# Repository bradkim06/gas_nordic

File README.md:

# Industrial Gas Monitor Firmware (nRF52832 + Zephyr)

Firmware version **1.0.2** for HHS's portable industrial gas monitor. The
application runs on a custom nRF52832 board, measures multiple gases, and
transmits real-time readings over Bluetooth® Low Energy. Environmental data is
fused with the Bosch BSEC2 library to provide indoor air-quality indicators in
addition to electrochemical gas concentrations.

---

## Table of contents

1. [Key features](#key-features)
2. [Hardware overview](#hardware-overview)
3. [Supported measurements](#supported-measurements)
4. [Firmware architecture](#firmware-architecture)
5. [Build and flash](#build-and-flash)
6. [Bluetooth protocol](#bluetooth-protocol)
7. [Calibration & persistent settings](#calibration--persistent-settings)
8. [Reference tables](#reference-tables)
9. [License](#license)

---

## Key features

- **Multi-gas sensing** – Electrochemical front-end for oxygen and a selectable
  toxic gas channel (NO₂, CO, H₂S, Cl₂, NH₃, etc.) with temperature
  compensation and dynamic calibration algorithms.【F:src/gas.c†L1-L212】
- **Environmental monitoring** – Integrated BME68x support with Bosch BSEC2
  fusion to derive temperature, humidity, pressure, IAQ, equivalent CO₂, and
  VOC indices. BSEC state is saved to flash for consistent long-term behavior.
  【F:drivers/bme68x_iaq/bme68x_iaq.c†L40-L460】【F:src/settings.c†L1-L137】
- **Bluetooth LE connectivity** – Custom 128-bit GATT service publishes
  semicolon-delimited measurements every 10 seconds and accepts configuration
  commands from a companion application.【F:src/bluetooth.h†L5-L45】【F:src/bluetooth.c†L520-L585】
- **Robust low-power platform** – Built on Zephyr RTOS (nRF Connect SDK v2.4.2)
  with watchdog, power management, persistent storage, and board-specific
  optimizations.【F:prj.conf†L1-L110】

## Hardware overview

- **Target SoC:** Nordic Semiconductor nRF52832 (ARM® Cortex®-M4F, BLE 5).
- **Custom board definition:** `boards/arm/hhs_nrf52832` (schematic and layout
  included in `doc/`).【F:boards/arm/hhs_nrf52832/hhs_nrf52832.yaml†L1-L53】
- **Latest hardware pack:** `doc/gas_nrf52832_rev1.0.1.pdf` with matching
  schematic `doc/gas_nrf52832_sch_rev0.1.0.pdf`.
- **Peripheral highlights:**
  - Bosch BME688/BME680 environmental sensor on I²C.
  - Dual-channel electrochemical sensor front-end via SAADC.
  - Battery gauge through voltage divider + ADC.
  - RGB status LED and watchdog support.

## Supported measurements

| Domain                | Reported values                                              |
| --------------------- | ------------------------------------------------------------ |
| Electrochemical gas   | Oxygen concentration (%VOL) and one selectable toxic gas in
|                       | ppm, both temperature compensated and filtered.【F:src/gas.c†L1-L212】 |
| Environmental         | Temperature (°C), relative humidity (%RH), barometric
|                       | pressure (Pa), IAQ score, equivalent CO₂ (ppm), and breath
|                       | VOC index via BSEC2.【F:drivers/bme68x_iaq/bme68x_iaq.c†L40-L460】 |
| Power                 | Battery percentage derived from loaded voltage profile.
| BLE telemetry         | Timestamped payload streamed every 10 seconds (default).

## Firmware architecture

The firmware is organized into cooperative Zephyr threads and kernel events. A
high-level flow is shown below:

```mermaid
---
title: Portable Gas Monitor Firmware Flow
---
stateDiagram-v2
    direction TB
    [*] --> ZephyrRTOS
    ZephyrRTOS --> BME68x_BSEC
    ZephyrRTOS --> Electrochemical_ADC
    ZephyrRTOS --> BluetoothLE

    state ZephyrRTOS {
        state BME68x_BSEC {
            direction LR
            initBSEC --> readEnvironmental : 3 s
            initBSEC --> computeIAQ : 60 s
        }
        state Electrochemical_ADC {
            direction TB
            sampleADC --> tempCompensation
            tempCompensation --> gasConversion
            gasConversion --> dynamicCalibration
        }
        state BluetoothLE {
            direction LR
            initialize --> advertise
            advertise --> connected
            connected --> notifyData : 10 s
        }
    }
```

Key modules reside in `src/` (application logic), `drivers/bme68x_iaq/`
(BSEC2 integration), and `lib/` (Bosch libraries). Threads communicate via
Zephyr events for deterministic BLE publishing and alarm handling.

## Build and flash

1. **Install prerequisites**
   - [nRF Connect SDK v2.4.2](https://developer.nordicsemi.com/nRF_Connect_SDK/doc/2.4.2/nrf/index.html)
     with the Zephyr toolchain, `west`, and SEGGER J-Link tools.
   - Bosch BSEC2 library files are already provided under `lib/`.
2. **Fetch the source**
   ```bash
   git clone https://github.com/<your-org>/gas_nordic.git
   cd gas_nordic
   west init -l .
   west update
   ```
3. **Build**
   ```bash
   west build -b hhs_nrf52832 .
   ```
   The output image is generated at `build/zephyr/zephyr.hex`.
4. **Flash**
   ```bash
   west flash
   ```
   or, to use Nordic's command-line tools directly:
   ```bash
   ./flash.sh
   ```
   (`flash.sh` performs a chip erase and programs the generated HEX via
   `nrfjprog`).【F:flash.sh†L1-L5】

## Bluetooth protocol

The device exposes a proprietary 128-bit primary service (`0000FFF0-0000-1000-8000-00805F9B34FB`).【F:src/bluetooth.h†L9-L26】

| Characteristic | UUID                                      | Properties | Description |
| -------------- | ----------------------------------------- | ---------- | ----------- |
| Measurement    | `0000FFF1-0000-1000-8000-00805F9B34FB`    | Notify     | Periodic payload `O2;Gas;Battery;Temp;Pressure;Humidity` separated by semicolons, integers scaled as `<val1>.<val2>` where applicable.【F:src/bluetooth.c†L536-L576】 |
| Command        | `0000FFF2-0000-1000-8000-00805F9B34FB`    | Write      | ASCII commands for calibration and configuration: `O2=<percent>`, `NO2=<ppm>`, `BT=<name>`.【F:src/bluetooth.c†L60-L124】 |

Notifications are issued when a connection is active and the client enables
CCCD. Each update corresponds to the latest sensor snapshot and is throttled to
the configured 10 s publishing interval.

## Calibration & persistent settings

- **Dynamic calibration** continuously refines oxygen and toxic gas baselines by
  monitoring derivative stability, expected ranges, and board temperature.
  Manual calibration can be triggered by writing to the command characteristic as
  described above.【F:src/gas.c†L1-L212】【F:src/bluetooth.c†L60-L124】
- **Persistent storage** uses Zephyr's settings/NVS subsystem to retain BSEC
  state, sensor calibration voltages, and the advertised Bluetooth name across
  reboots.【F:src/settings.c†L1-L200】
- **Battery reporting** samples SAADC channels and converts them into a
  percentage using empirically tuned thresholds (see `src/battery.c`).

## Reference tables

### Oxygen concentration guide

| Category                    | Concentration range | Notes |
| --------------------------- | ------------------- | ----- |
| High oxygen                 | &gt; 24 %             | Elevated combustion risk. |
| Normal air                  | 20.9 %              | Nominal breathable atmosphere. |
| Elevated exposure risk      | 19.5 – 20.9 %       | Monitor for dilution hazards. |
| Low oxygen                  | 16 – 19.5 %         | Impaired cognition and physical performance. |
| Anoxic                      | &lt; 16 %             | Life-threatening within minutes. |

### Indoor air quality (IAQ) interpretation

| IAQ index | Air quality           | Suggested action |
| --------- | --------------------- | ---------------- |
| 0 – 50    | Excellent             | None required. |
| 51 – 100  | Good                  | None required. |
| 101 – 150 | Lightly polluted      | Ventilate if convenient. |
| 151 – 200 | Moderately polluted   | Increase ventilation with clean air. |
| 201 – 250 | Heavily polluted      | Identify contamination source, improve airflow. |
| 251 – 350 | Severely polluted     | Restrict access, maximize ventilation. |
| &gt; 351    | Extremely polluted    | Avoid occupancy until levels normalize. |

### CO₂ comfort levels

| Level | Description                        | ppm |
| :---: | ---------------------------------- | --- |
| 😆    | Healthy outdoor reference          | 350 |
| 😀    | Healthy indoor climate             | 600 |
| 🙂    | Acceptable indoors                 | 800 |
| 🙁    | Ventilation desirable              | 1000 |
| 😩    | Ventilation necessary              | 1200 |
| 😡    | Noticeable health effects          | 2000 |
| ⚠️    | Dangerous for prolonged exposure | 5000 |

### VOC hygiene guidance

| Rating    | Recommendation                                 | Exposure duration | TVOC (ppm) |
| --------- | ---------------------------------------------- | ----------------- | ---------- |
| Excellent | Target value                                    | Unlimited         | 0 – 0.065 |
| Good      | Ventilation recommended                         | Unlimited         | 0.065 – 0.22 |
| Moderate  | Increase ventilation, inspect for sources       | &lt; 12 months       | 0.22 – 0.66 |
| Poor      | Intensify ventilation, locate emission sources  | &lt; 1 month         | 0.66 – 2.2 |
| Unhealthy | Immediate ventilation required                  | Hours             | 2.2 – 5.5 |

## License

Distributed under the terms of the [MIT License](LICENSE). Bosch BSEC2 library
usage is subject to its proprietary license (see `lib/Bosch-BSEC2-Library`).

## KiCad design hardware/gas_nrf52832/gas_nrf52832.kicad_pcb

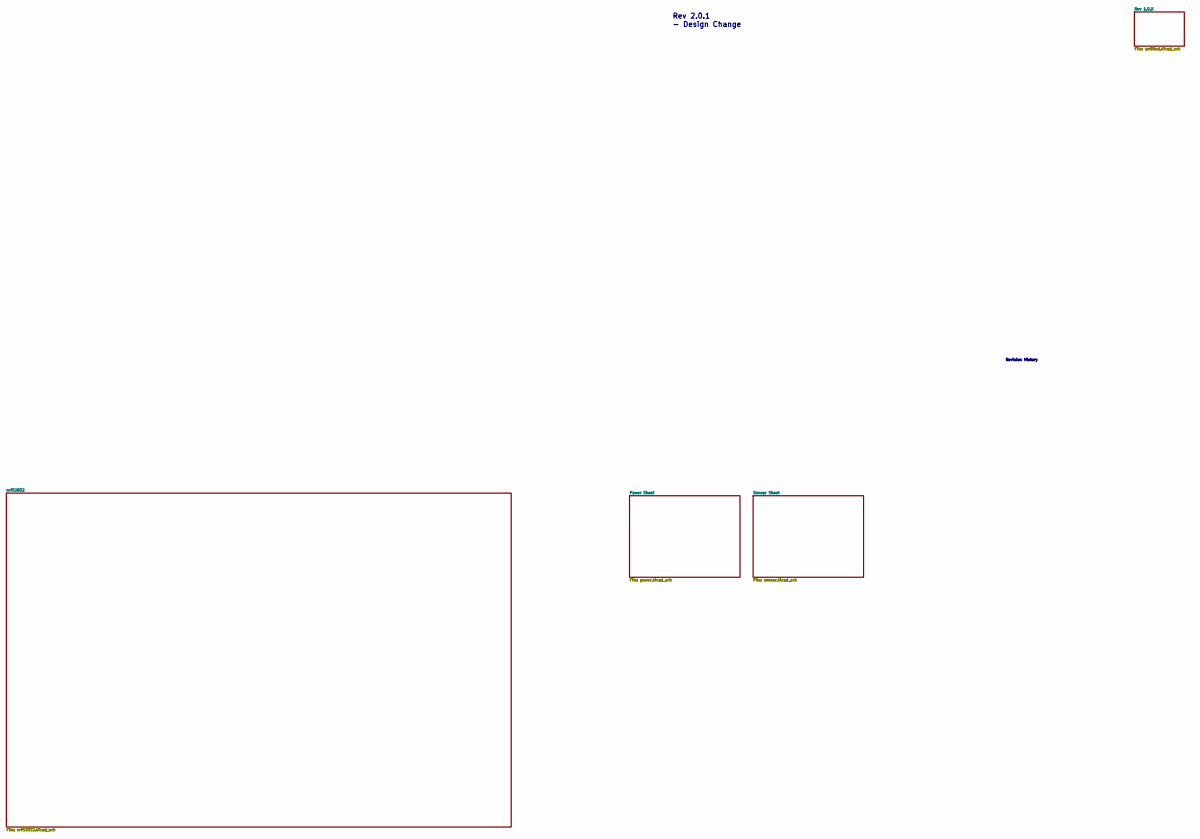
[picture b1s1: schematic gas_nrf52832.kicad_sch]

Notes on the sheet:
Revision History
Rev 2.0.1 - Design Change

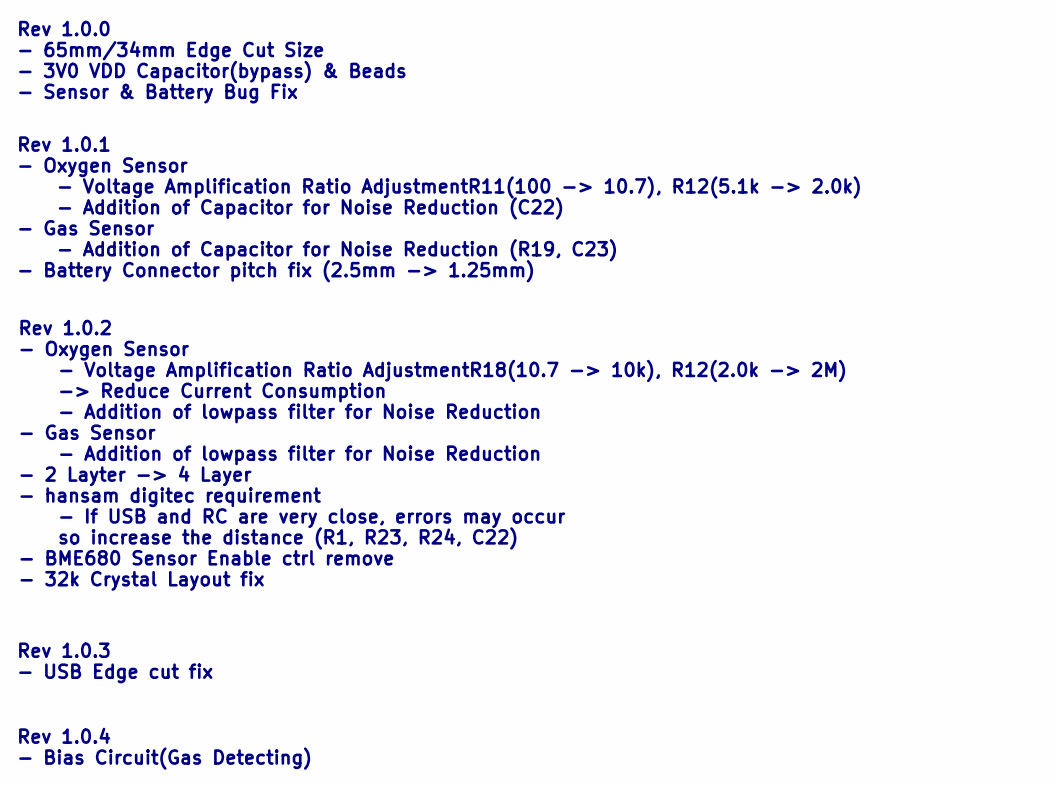
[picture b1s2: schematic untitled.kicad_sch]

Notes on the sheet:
Rev 1.0.2 - Oxygen Sensor - Voltage Amplification Ratio AdjustmentR18(10.7 -> 10k), R12(2.0k -> 2M) -> Reduce Current Consumption - Addition of lowpass filter for Noise Reduction - Gas Sensor - Addition of lowpass filter for Noise Reduction - 2 Layter -> 4 Layer - hansam digitec requirement - If US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
Rev 1.0.3 - USB Edge cut fix
Rev 1.0.0 - 65mm/34mm Edge Cut Size - 3V0 VDD Capacitor(bypass) & Beads - Sensor & Battery Bug Fix
Rev 1.0.1 - Oxygen Sensor - Voltage Amplification Ratio AdjustmentR11(100 -> 10.7), R12(5.1k -> 2.0k) - Addition of Capacitor for Noise Reduction (C22) - Gas Sensor - Addition of Capacitor for Noise Reduction (R19, C23) - Battery Connector pitch fix (2.5mm -> 1.25mm)
Rev 1.0.4 - Bias Circuit(Gas Detecting)

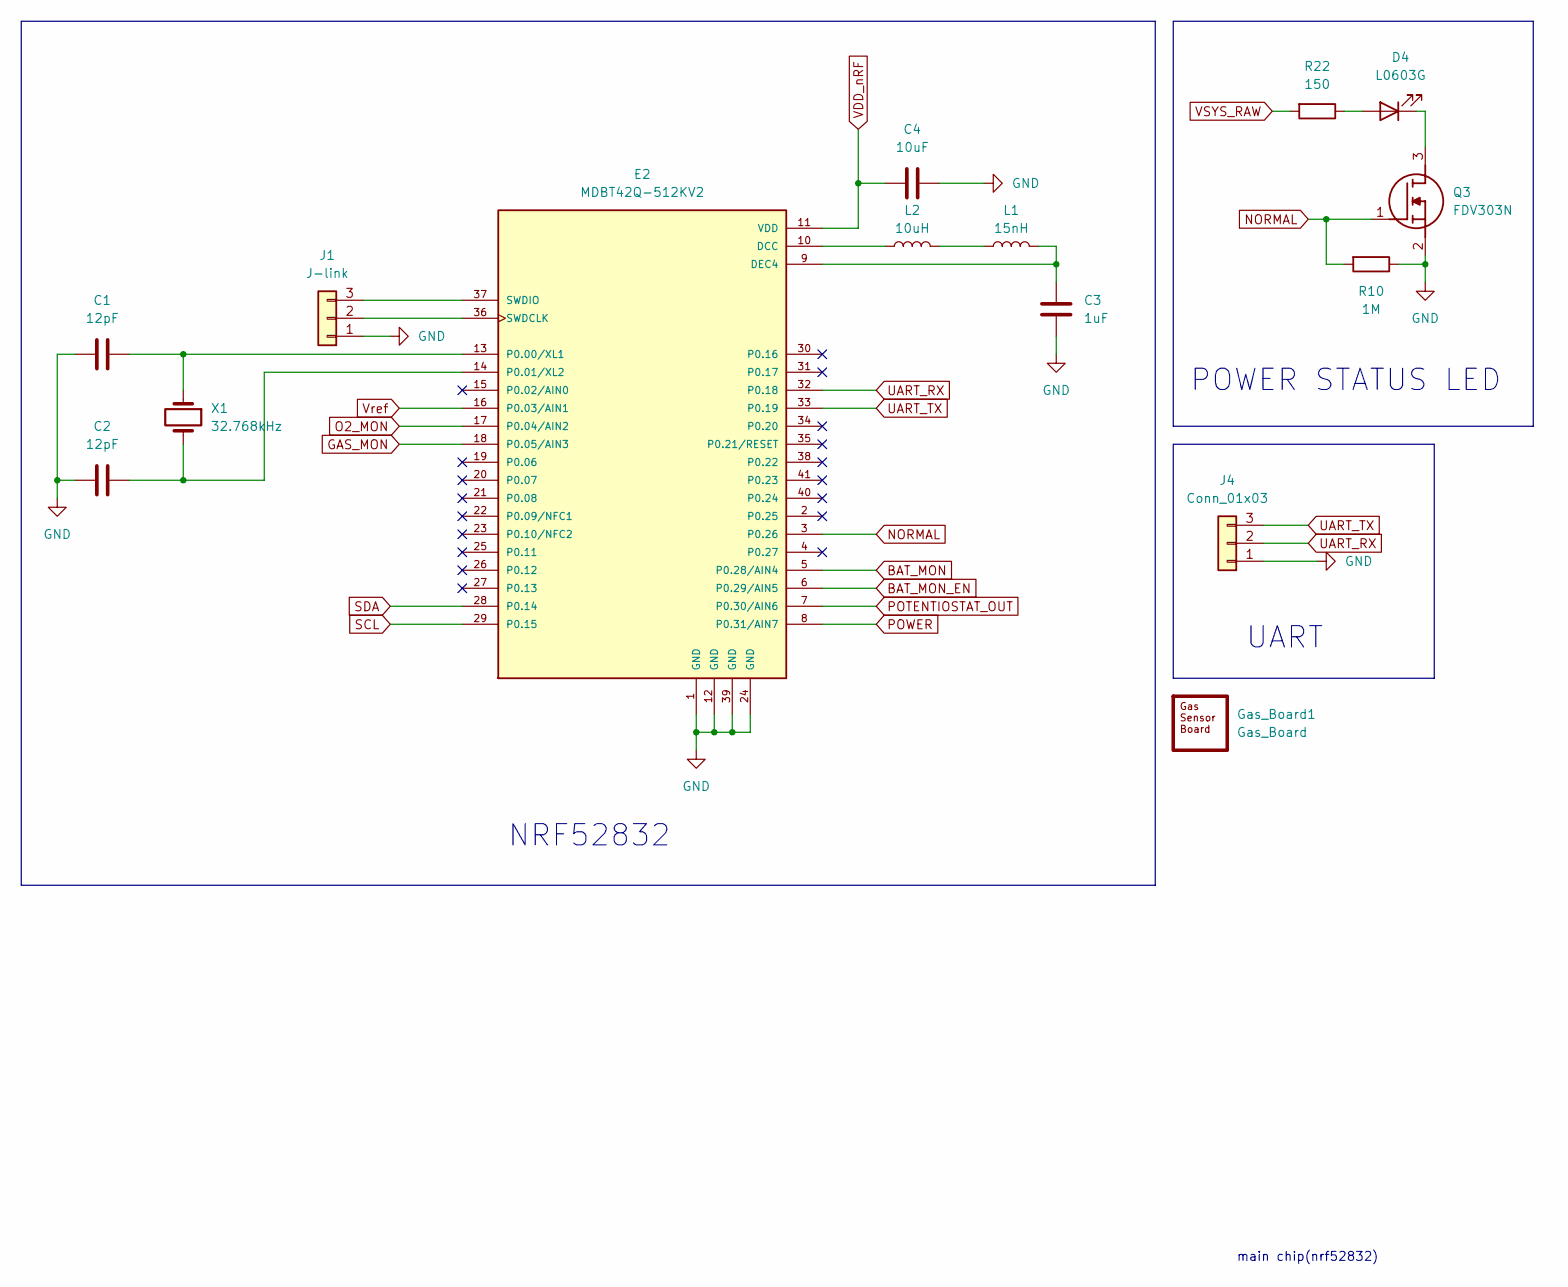
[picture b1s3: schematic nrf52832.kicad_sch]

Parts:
C1, C2: 12pF; C_0402_1005Metric; Manufacturer_Part_Number CL05C120JB5NNNC
C3: 1uF; C_0402_1005Metric; Manufacturer_Part_Number GRM155C71A105ME11D
C4: 10uF; C_0402_1005Metric; Manufacturer_Part_Number GRM155C80J106ME11D
D4: L0603G; WP1533BQ; Manufacturer_Part_Number WP1533BQ/GD
E2: MDBT42Q-512KV2; RAYTAC_MDBT42Q-512KV2; PARTREV J
Gas_Board1: Gas_Board; gas_nordic_edge
J1: J-link; PinHeader_1x03_P2.54mm_Vertical
J4: Conn_01x03; PinHeader_1x03_P2.54mm_Vertical
L1: 15nH; L_0402_1005Metric; Manufacturer_Part_Number MLG1005S15NJT000
L2: 10uH; L_0603_1608Metric; Manufacturer_Part_Number LQM18FN100M00D
Q3: FDV303N; SOT96P237X111-3N; Manufacturer_Part_Number FDV303N; Mouser Part Number 512-FDV303N
R10: 1M; R_0402_1005Metric; Manufacturer_Part_Number RC0402FR-071ML
R22: 150; R_0402_1005Metric; Manufacturer_Part_Number RM04FTN1500
X1: 32.768kHz; Crystal_SMD_3215-2Pin_3.2x1.5mm; Manufacturer_Part_Number FC-135 32.7680KA-A5

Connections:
BAT_MON: E2.5 (P0.28/AIN4); also elsewhere on the board
BAT_MON_EN: E2.6 (P0.29/AIN5); also elsewhere on the board
GAS_MON: E2.18 (P0.05/AIN3); also elsewhere on the board
GND: C1.1, C2.1, C3.2, C4.2, E2.1 (GND), E2.12 (GND), E2.24 (GND), E2.39 (GND), J1.1, J4.1, Q3.2 (S), R10.1; also elsewhere on the board
NORMAL: E2.3 (P0.26), Q3.1 (G), R10.2
unnamed: D4.2 (A), R22.1
unnamed: D4.1 (K), Q3.3 (D)
unnamed: E2.10 (DCC), L2.1
unnamed: C3.1, E2.9 (DEC4), L1.2
unnamed: C1.2, E2.13 (P0.00/XL1), X1.1
unnamed: C2.2, E2.14 (P0.01/XL2), X1.2
unnamed: E2.36 (SWDCLK), J1.2
unnamed: E2.37 (SWDIO), J1.3
unnamed: L1.1, L2.2
O2_MON: E2.17 (P0.04/AIN2); also elsewhere on the board
POTENTIOSTAT_OUT: E2.7 (P0.30/AIN6); also elsewhere on the board
POWER: E2.8 (P0.31/AIN7); also elsewhere on the board
SCL: E2.29 (P0.15); also elsewhere on the board
SDA: E2.28 (P0.14); also elsewhere on the board
UART_RX: E2.32 (P0.18), J4.2
UART_TX: E2.33 (P0.19), J4.3
VDD_nRF: C4.1, E2.11 (VDD); also elsewhere on the board
VSYS_RAW: R22.2; also elsewhere on the board
Vref: E2.16 (P0.03/AIN1); also elsewhere on the board

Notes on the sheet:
main chip(nrf52832)
NRF52832
UART
POWER STATUS LED

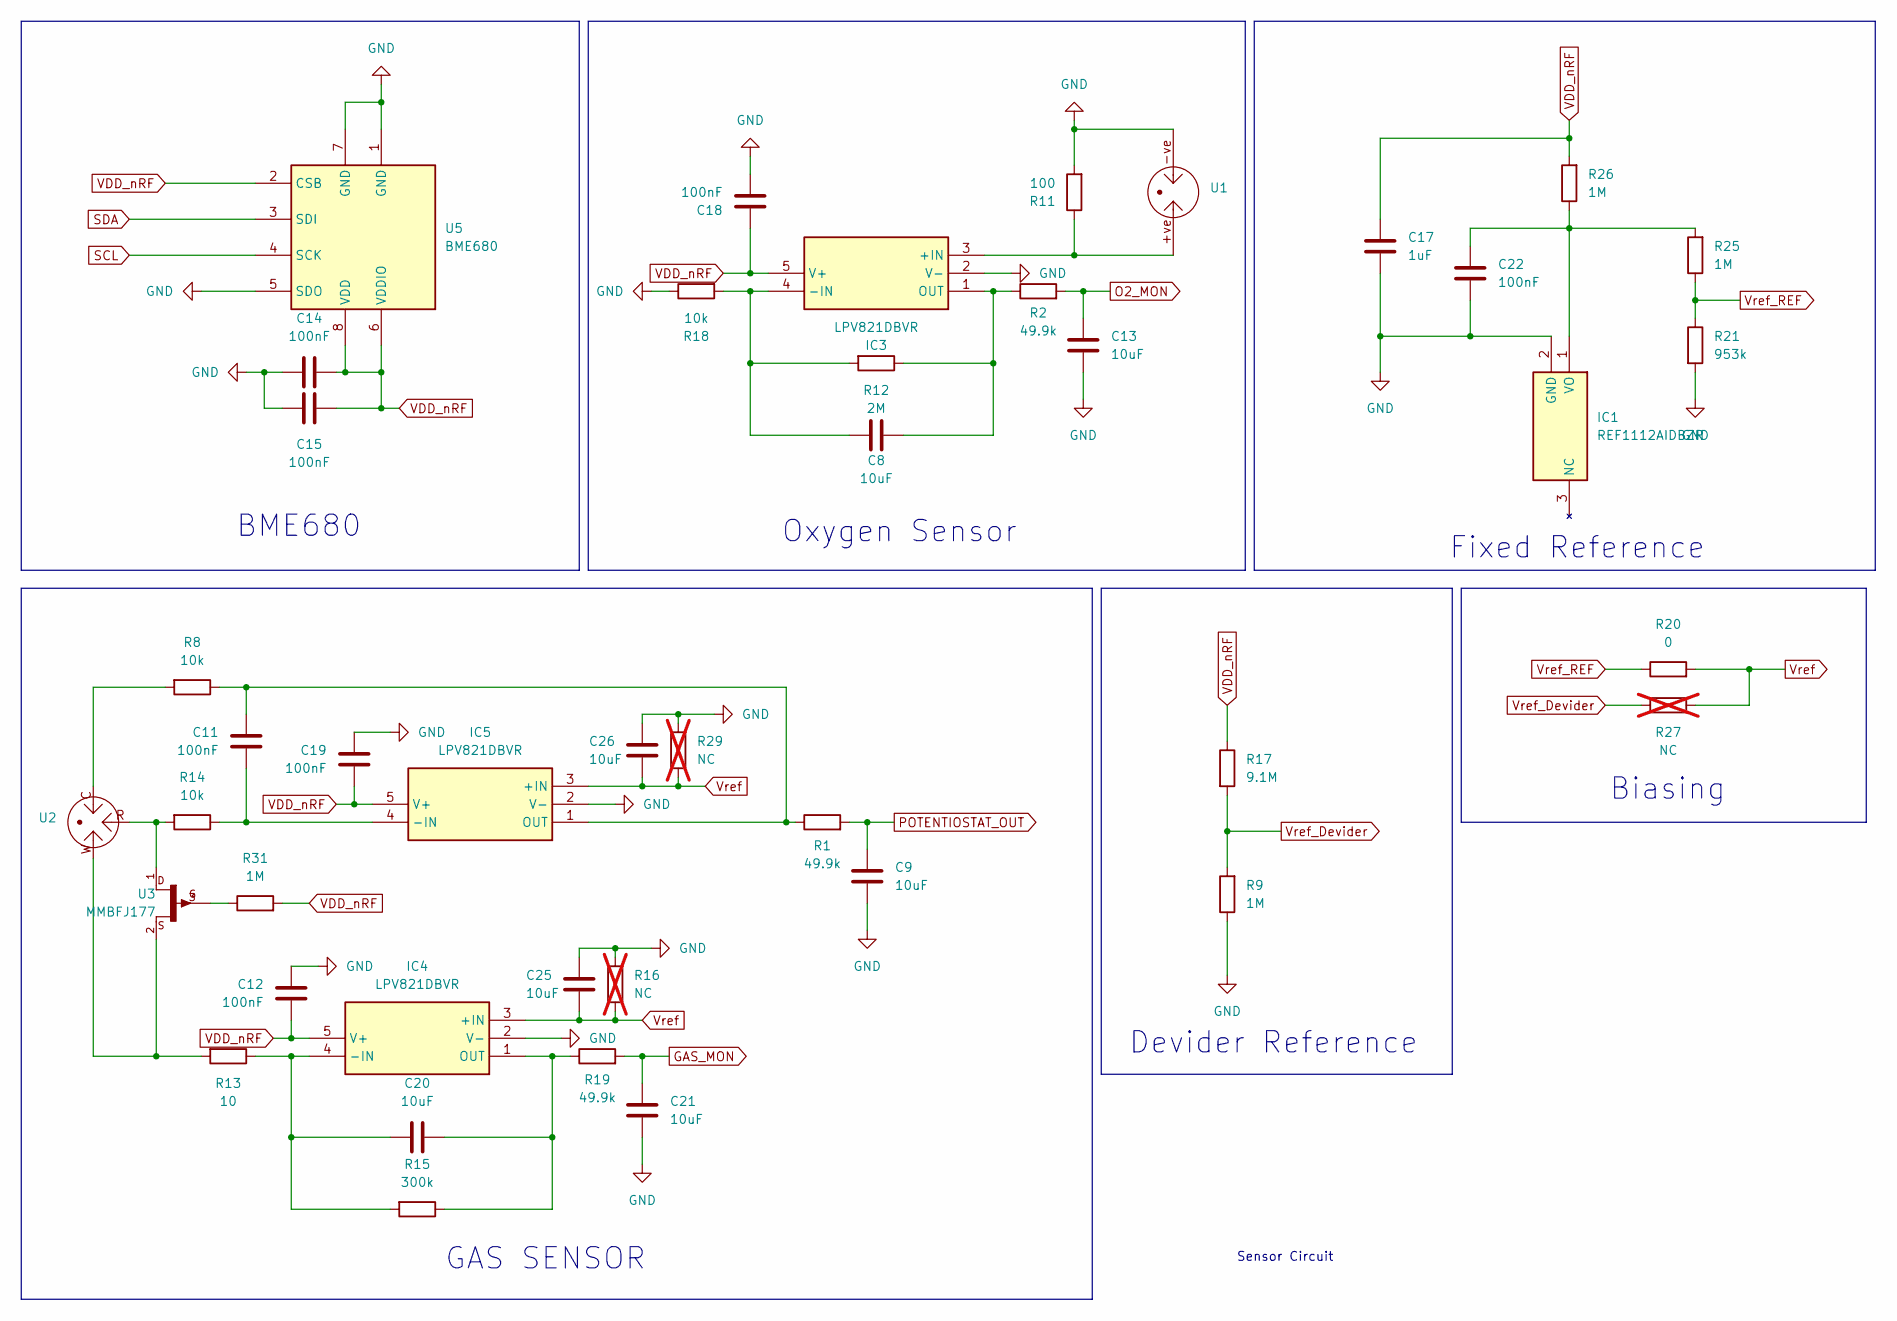
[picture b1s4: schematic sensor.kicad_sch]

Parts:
C8, C9, C13, C20, C21, C25, C26: 10uF; C_0402_1005Metric; Manufacturer_Part_Number GRM155C80J106ME11D
C11, C12, C14, C15, C18, C19, C22: 100nF; C_0402_1005Metric; Manufacturer_Part_Number CL05B104KO5NNNC
C17: 1uF; C_0402_1005Metric; Manufacturer_Part_Number GRM155C71A105ME11D
IC1: REF1112AIDBZR; SOT95P237X112-3N; Manufacturer_Part_Number REF1112AIDBZR; Mouser Part Number 595-REF1112AIDBZR
IC3, IC4, IC5: LPV821DBVR; SOT95P280X145-5N; Manufacturer_Part_Number LPV821DBVR; Mouser Part Number 595-LPV821DBVR
R1, R2, R19: 49.9k; R_0402_1005Metric; Manufacturer_Part_Number RM04FTN4992
R8, R14, R18: 10k; R_0402_1005Metric; Manufacturer_Part_Number RM04FTN1002
R9, R25, R26, R31: 1M; R_0402_1005Metric; Manufacturer_Part_Number RC0402FR-071ML
R11: 100; R_0402_1005Metric; Manufacturer_Part_Number RC0402FR-07100RL
R12: 2M; R_0402_1005Metric; Manufacturer_Part_Number RC0402FR-072ML
R13: 10; R_0402_1005Metric; Manufacturer_Part_Number RC0402FR-0710RL
R15: 300k; R_0402_1005Metric; Manufacturer_Part_Number WR04X3003FTL
R16, R27, R29: NC; R_0402_1005Metric; not fitted
R17: 9.1M; R_0603_1608Metric; Manufacturer_Part_Number WR06W9104FTL
R20: 0; R_0402_1005Metric; Manufacturer_Part_Number RM04JTN0
R21: 953k; R_0603_1608Metric; Manufacturer_Part_Number WR06X9533FTL
U1: SS2118_O2
U2: SS2198_H2S
U3: MMBFJ177; SOT23; Manufacturer_Part_Number MMBFJ177LT1G
U5: BME680; Bosch_LGA-8_3x3mm_P0.8mm_ClockwisePinNumbering; Manufacturer_Part_Number BME680

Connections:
GAS_MON: C21.2, R19.2; also elsewhere on the board
GND: C9.1, C12.1, C13.1, C14.1, C15.1, C17.1, C18.1, C19.1, C21.1, C22.1, C25.2, C26.2, IC1.2 (GND), IC3.2 (V-), IC4.2 (V-), IC5.2 (V-), R9.1, R11.2, R16.2, R18.1, R21.2, R29.2, U1.-ve, U5.1 (GND), U5.5 (SDO), U5.7 (GND); also elsewhere on the board
unnamed: C22.2, IC1.1 (VO), R25.2, R26.1
unnamed: IC3.3 (+IN), R11.1, U1.+ve
unnamed: C8.2, IC3.4 (-IN), R12.2, R18.2
unnamed: C8.1, IC3.1 (OUT), R2.1, R12.1
unnamed: C20.2, IC4.4 (-IN), R13.1, R15.2
unnamed: C20.1, IC4.1 (OUT), R15.1, R19.1
unnamed: C11.2, IC5.4 (-IN), R14.1
unnamed: C11.1, IC5.1 (OUT), R1.1, R8.1
unnamed: R8.2, U2.C
unnamed: R13.2, U2.W, U3.2
unnamed: R14.2, U2.R, U3.1
unnamed: R31.1, U3.3
O2_MON: C13.2, R2.2; also elsewhere on the board
POTENTIOSTAT_OUT: C9.2, R1.2; also elsewhere on the board
SCL: U5.4 (SCK); also elsewhere on the board
SDA: U5.3 (SDI); also elsewhere on the board
VDD_nRF: C12.2, C14.2, C15.2, C17.2, C18.2, C19.2, IC3.5 (V+), IC4.5 (V+), IC5.5 (V+), R17.1, R26.2, R31.2, U5.2 (CSB), U5.6 (VDDIO), U5.8 (VDD); also elsewhere on the board
Vref: C25.1, C26.1, IC4.3 (+IN), IC5.3 (+IN), R16.1, R20.2, R27.2, R29.1; also elsewhere on the board
Vref_Devider: R9.2, R17.2, R27.1
Vref_REF: R20.1, R21.1, R25.1

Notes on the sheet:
GAS SENSOR
Biasing
Oxygen Sensor
Fixed Reference
BME680
Devider Reference
Sensor Circuit

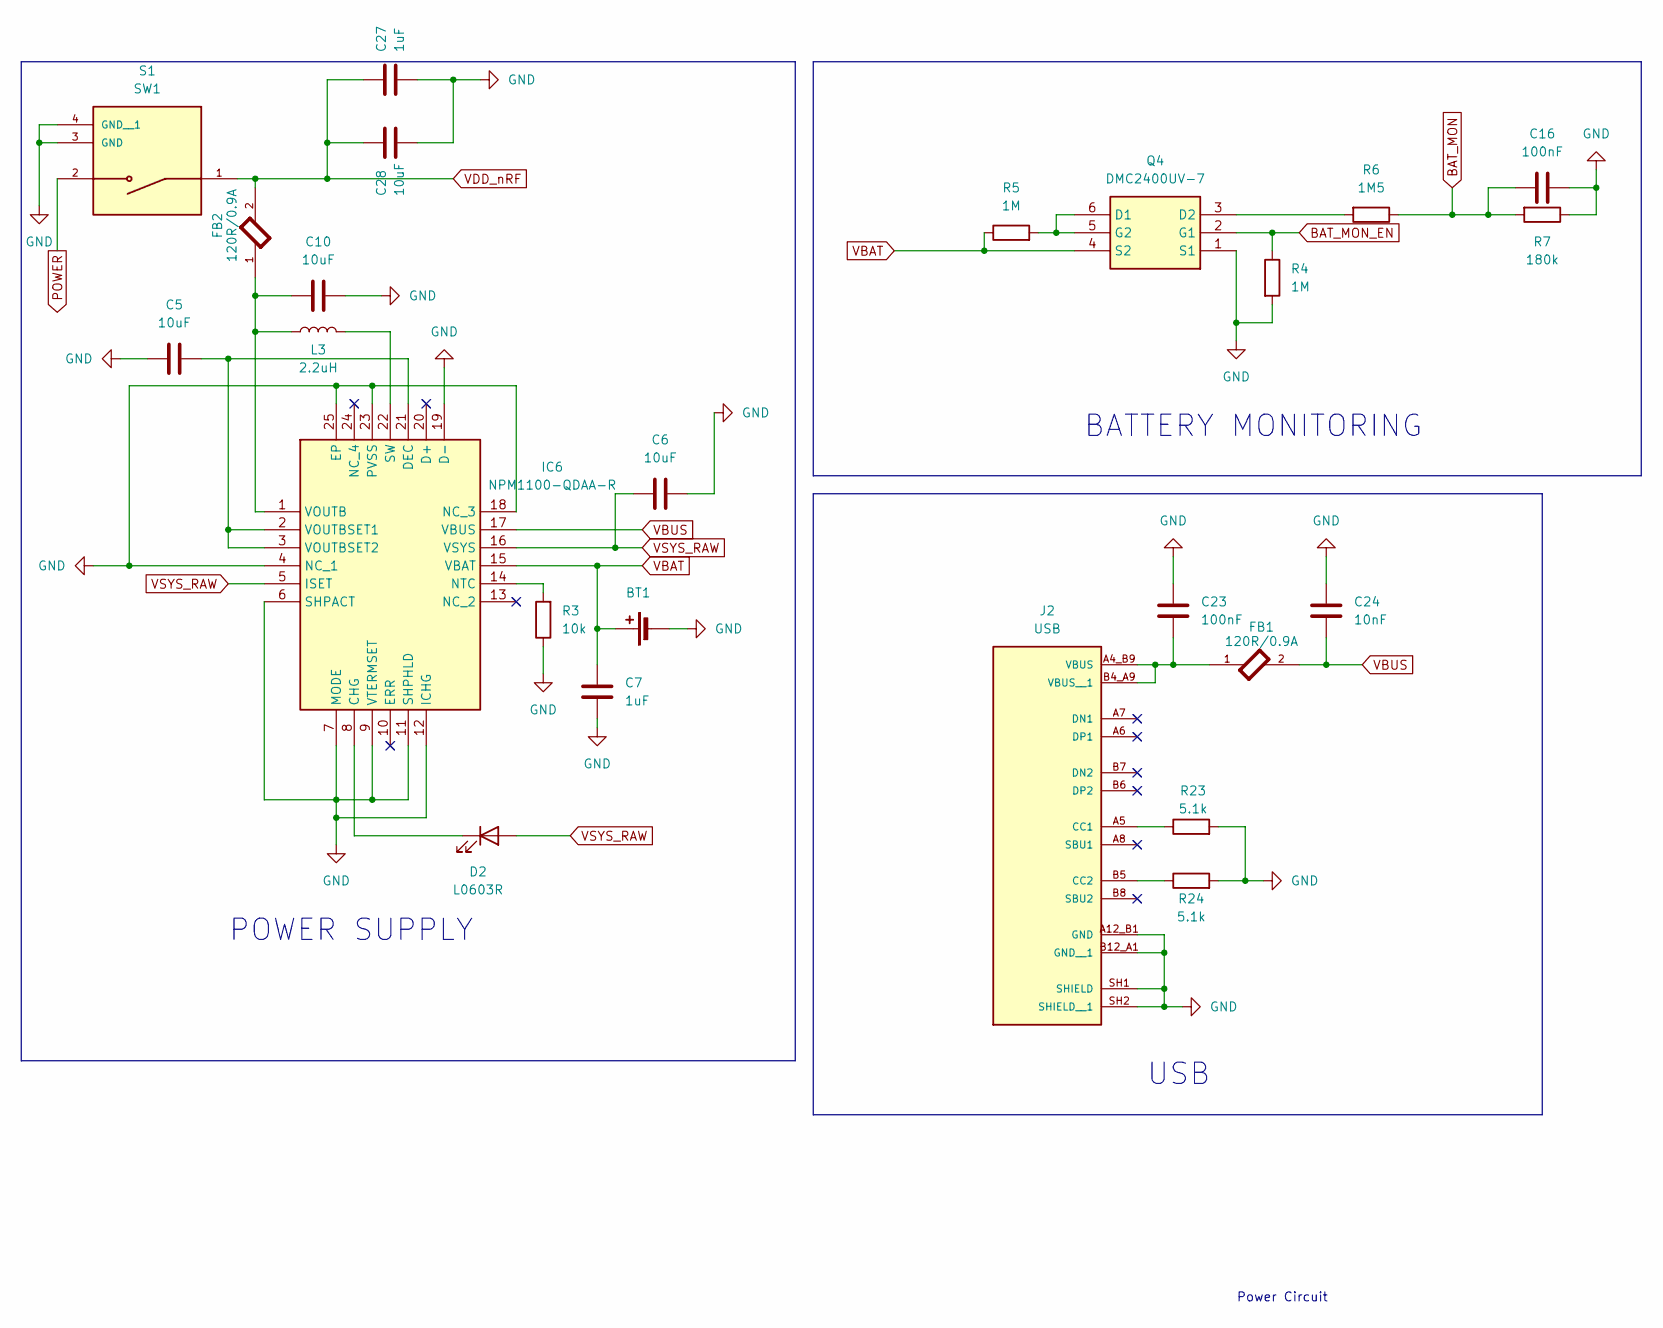
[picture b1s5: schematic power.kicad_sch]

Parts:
BT1: BT1; PinHeader_1x02_P1.27mm_Vertical
C5, C6, C10, C28: 10uF; C_0402_1005Metric; Manufacturer_Part_Number GRM155C80J106ME11D
C7, C27: 1uF; C_0402_1005Metric; Manufacturer_Part_Number GRM155C71A105ME11D
C16, C23: 100nF; C_0402_1005Metric; Manufacturer_Part_Number CL05B104KO5NNNC
C24: 10nF; C_0402_1005Metric; Manufacturer_Part_Number CL05B103KB5NNNC
D2: L0603R; WP1533BQ; Manufacturer_Part_Number WP1533BQ/ID
FB1, FB2: 120R/0.9A; MURATA_BLM15PE121SH1D_0; Manufacturer_Part_Number BLM15PE121SH1D; DigiKey_Part_Number 490-BLM15PE121SH1DTR-ND
IC6: NPM1100-QDAA-R; QFN50P400X400X90-25N-D; Manufacturer_Part_Number NPM1100-QDAA-R; Mouser Part Number 949-NPM1100-QDAA-R
J2: USB; CUI_UJ20-C-G-MSMT-TR-68; PARTREV 1.0
L3: 2.2uH; 1285ASH1R0MP2; Manufacturer_Part_Number 1285AS-H-2R2M=P2
Q4: DMC2400UV-7; SOTFL50P162X60-6N; Manufacturer_Part_Number DMC2400UV-7; Mouser Part Number N/A
R3: 10k; R_0402_1005Metric; Manufacturer_Part_Number RM04FTN1002
R4, R5: 1M; R_0402_1005Metric; Manufacturer_Part_Number RC0402FR-071ML
R6: 1M5; R_0402_1005Metric; Manufacturer_Part_Number RC0402FR-071M5L
R7: 180k; R_0402_1005Metric; Manufacturer_Part_Number RM04FTN1803
R23, R24: 5.1k; R_0402_1005Metric; Manufacturer_Part_Number RM04FTN5101
S1: SW1; SW_TS11-674-43-BK-100-RA-D; PARTREV 1.01

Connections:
BAT_MON: C16.1, R6.1, R7.2; also elsewhere on the board
BAT_MON_EN: Q4.2 (G1), R4.1; also elsewhere on the board
GND: BT1.2 (-), C5.1, C6.2, C7.1, C10.2, C16.2, C23.1, C24.1, C27.1, C28.1, IC6.4 (NC_1), IC6.6 (SHPACT), IC6.7 (MODE), IC6.9 (VTERMSET), IC6.11 (SHPHLD), IC6.12 (ICHG), IC6.18 (NC_3), IC6.19 (D-), IC6.23 (PVSS), IC6.25 (EP), J2.A12_B1 (GND), J2.B12_A1 (GND__1), J2.SH1 (SHIELD), J2.SH2 (SHIELD__1), Q4.1 (S1), R3.1, R4.2, R7.1, R23.2, R24.2, S1.3 (GND), S1.4 (GND__1); also elsewhere on the board
unnamed: D2.1 (K), IC6.8 (CHG)
unnamed: C5.2, IC6.2 (VOUTBSET1), IC6.3 (VOUTBSET2), IC6.21 (DEC)
unnamed: IC6.14 (NTC), R3.2
unnamed: IC6.22 (SW), L3.2
unnamed: C10.1, FB2.1, IC6.1 (VOUTB), L3.1
unnamed: J2.A5 (CC1), R23.1
unnamed: J2.B5 (CC2), R24.1
unnamed: C23.2, FB1.1, J2.A4_B9 (VBUS), J2.B4_A9 (VBUS__1)
unnamed: Q4.5 (G2), Q4.6 (D1), R5.2
unnamed: Q4.3 (D2), R6.2
POWER: S1.2; also elsewhere on the board
VBAT: BT1.1 (+), C7.2, IC6.15 (VBAT), Q4.4 (S2), R5.1
VBUS: C24.2, FB1.2, IC6.17 (VBUS)
VDD_nRF: C27.2, C28.2, FB2.2, S1.1; also elsewhere on the board
VSYS_RAW: C6.1, D2.2 (A), IC6.5 (ISET), IC6.16 (VSYS); also elsewhere on the board

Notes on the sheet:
Power Circuit
POWER SUPPLY
BATTERY MONITORING
USB

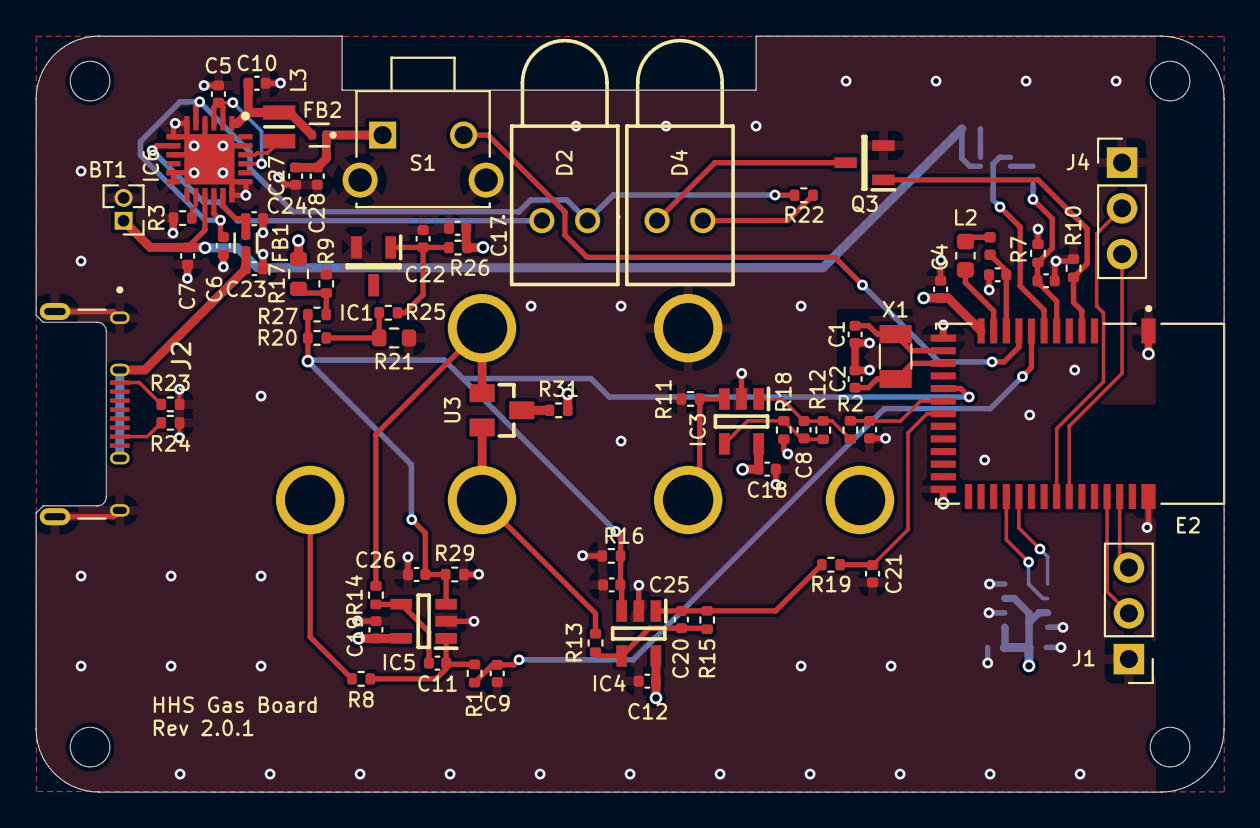
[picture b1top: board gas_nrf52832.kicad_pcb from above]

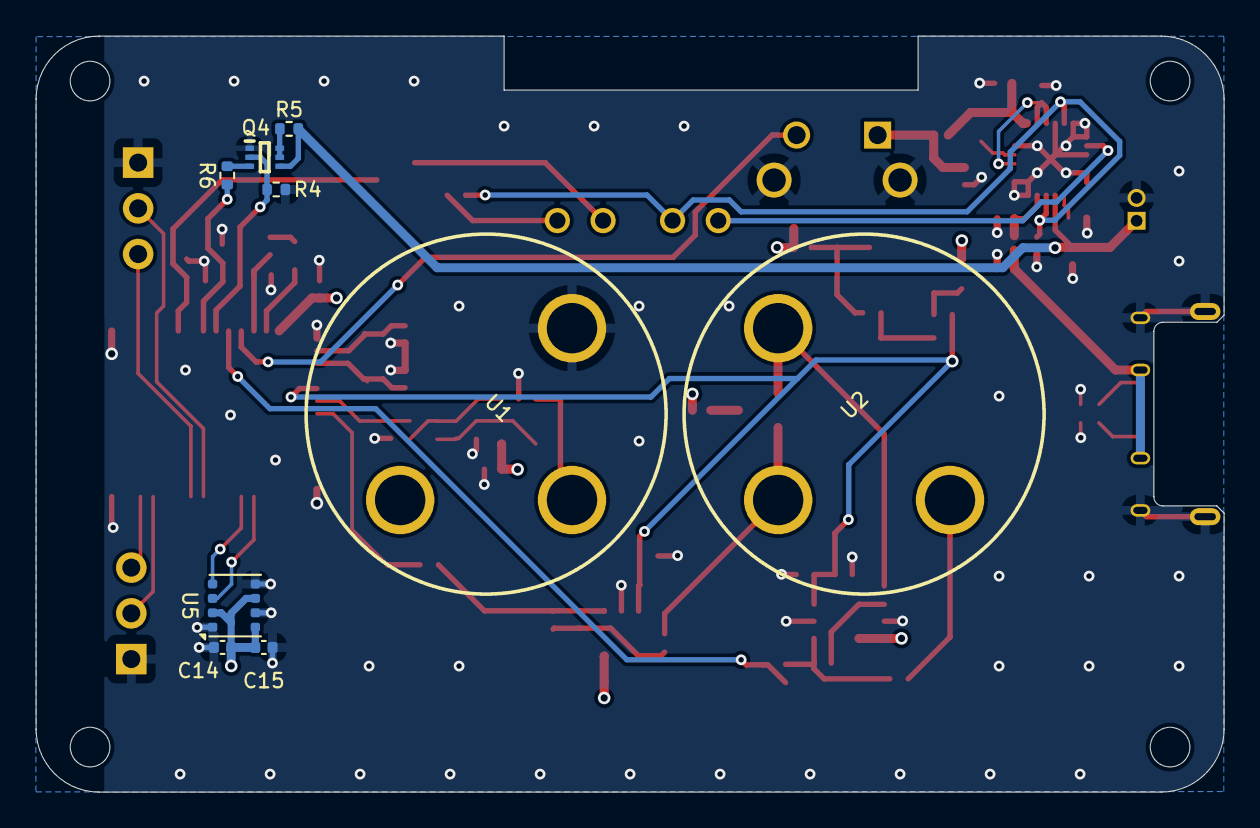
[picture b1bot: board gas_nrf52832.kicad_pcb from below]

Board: 4 copper layers, 66.0 x 42.0 mm, 83 parts (9 on the bottom side), 50 nets.

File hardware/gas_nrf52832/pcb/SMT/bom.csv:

"Reference","Value","Qty","MANUFACTURER","Manufacturer_Part_Number","설명","Package","Type"
"X1","32.768kHz","1","EPSON","FC-135 32.7680KA-A5","Crystals SMD 32.768kHz","SMD3215-2P","Surface Mount "
"U5","BME680","1","Bosch Sensortec","BME680","Pressure Sensors ROHS","LGA-8","Surface Mount "
"U3","MMBFJ177","1","onsemi","MMBFJ177LT1G","JFET P-Channel 30 V 225 mW Surface Mount SOT-23-3 (TO-236)","SOT-23-3","Surface Mount "
"R23,R24","5.1k","2","TA-I Tech","RM04FTN5101","Fixed Resistor, Metal Glaze/thick Film, 0.0625W, 5.1k ohm, 50V, 1% +/-Tol, 100ppm/Cel","0402 (1005 Metric)","Surface Mount "
"R22","150","1","TA-I Tech","RM04FTN1500","Fixed Resistor, Metal Glaze/thick Film, 0.0625W, 150 ohm, 50V, 1% +/-Tol, 100ppm/Cel","0402 (1005 Metric)","Surface Mount "
"R21","953k","1","WALSIN","WR06X9533FTL","953 kOhms ±1% 0.1W, 1/10W Chip Resistor 0603 (1608 Metric) Thick Film","0603 (1608 Metric)","Surface Mount "
"R20","0","1","TA-I Tech","RM04JTN0","62.5mW Thick Film Resistors 50V ±100ppm/℃ ±5% 0Ω 0402  Chip Resistor - Surface Mount ROHS","0402 (1005 Metric)","Surface Mount "
"R17","9.1M","1","WALSIN","WR06W9104FTL","RES 9.1M OHM 1% 0603","0603 (1608 Metric)","Surface Mount "
"R15","300k","1","WALSIN","WR04X3003FTL","300 kOhms ±1% 0.063W, 1/16W Chip Resistor 0402 (1005 Metric) Thick Film","0402 (1005 Metric)","Surface Mount "
"R13","10","1","YAGEO","RC0402FR-0710RL","62.5mW Thick Film Resistors 50V ±1% ±200ppm/℃ 10Ω 0402  Chip Resistor - Surface Mount ROHS","0402 (1005 Metric)","Surface Mount "
"R12","2M","1","YAGEO","RC0402FR-072ML","62.5mW Thick Film Resistors 50V ±100ppm/℃ ±1% 2MΩ 0402  Chip Resistor - Surface Mount ROHS","0402 (1005 Metric)","Surface Mount "
"R11","100","1","YAGEO","RC0402FR-07100RL","62.5mW Thick Film Resistors 50V ±100ppm/℃ ±1% 100Ω 0402  Chip Resistor - Surface Mount ROHS","0402 (1005 Metric)","Surface Mount "
"R7","180k","1","TA-I Tech","RM04FTN1803","Fixed Resistor, Metal Glaze/thick Film, 0.0625W, 180k ohm, 50V, 1% +/-Tol, 100ppm/Cel","0402 (1005 Metric)","Surface Mount "
"R6","1M5","1","YAGEO","RC0402FR-071M5L","62.5mW Thick Film Resistors 50V ±100ppm/℃ ±1% 1.5MΩ 0402  Chip Resistor - Surface Mount ROHS","0402 (1005 Metric)","Surface Mount "
"R4,R5,R9,R10,R25,R26,R31","1M","7","YAGEO","RC0402FR-071ML","62.5mW Thick Film Resistors 50V ±100ppm/℃ ±1% 1MΩ 0402  Chip Resistor - Surface Mount ROHS","0402 (1005 Metric)","Surface Mount "
"R3,R8,R14,R18","10k","4","TA-I Tech","RM04FTN1002","Fixed Resistor, Metal Glaze/thick Film, 0.0625W, 10k ohm, 50V, 1% +/-Tol, 100ppm/Cel","0402 (1005 Metric)","Surface Mount "
"R1,R2,R19","49.9k","3","TA-I Tech","RM04FTN4992","62.5mW Thick Film Resistors 50V ±100ppm/℃ ±1% 49.9kΩ 0402  Chip Resistor - Surface Mount ROHS","0402 (1005 Metric)","Surface Mount "
"Q4","DMC2400UV-7","1","Diodes Incorporated ","DMC2400UV-7","20V 480mΩ@200mA,5V 450mW 900mV@250uA 1PCSNChannel+1PCSPChannel SOT-563  MOSFETs ROHS","SOT-563","Surface Mount "
"Q3","FDV303N","1","ONSEMI ","FDV303N","FDV303N N-Channel MOSFET, 680 mA, 25 V, 3-Pin SOT-23 ON Semiconductor","SOT-23","Surface Mount "
"L3","2.2uH","1","Murata Electronics","1285AS-H-2R2M=P2","1.5A 2.2uH ±20% 0806  Power Inductors ROHS","0806 (2016 Metric)","Surface Mount "
"L2","10uH","1","Murata Electronics","LQM18FN100M00D","50mA 10uH ±20% 50mA 1.17Ω 0603  Inductors (SMD) ROHS","0603 (1608 Metric)","Surface Mount "
"L1","15nH","1","TDK","MLG1005S15NJT000","400mA 15nH ±5% 350mΩ 0402  Inductors (SMD) ROHS","0402 (1005 Metric)","Surface Mount "
"IC6","NPM1100-QDAA-R","1","NORDIC SEMICONDUCTOR","NPM1100-QDAA-R","Lithium-Ion/Polymer Battery Management ROHS ","QFN-24(4x4)","Surface Mount "
"IC3,IC4,IC5","LPV821DBVR","3","Texas Instruments","LPV821DBVR","8kHz 1.5uV 7pA Single Channel Precision Op Amps ROHS","SOT-23-5","Surface Mount "
"IC1","REF1112AIDBZR","1","Texas Instruments","REF1112AIDBZR","Shunt Voltage Reference IC Fixed 1.25V V ±0.2% 5 mA SOT-23-3","SOT-23-3","Surface Mount "
"FB1,FB2","120R/0.9A","2","Murata Electronics ","BLM15PE121SH1D","FERRITE BEAD","0402 (1005 Metric) ","Surface Mount "
"E2","MDBT42Q-512KV2","1","Raytac","MDBT42Q-512KV2","Bluetooth Bluetooth v5.2 Transceiver Module","SMD-41","Surface Mount "
"C24","10nF","1","Samsung Electro-Mechanics","CL05B103KB5NNNC","50V 10nF X7R ±10% 0402  Multilayer Ceramic Capacitors MLCC - SMD/SMT ROHS","0402 (1005 Metric)","Surface Mount "
"C11,C12,C14,C15,C16,C18,C19,C22,C23","100nF","9","Samsung Electro-Mechanics","CL05B104KO5NNNC","16V 100nF X7R ±10% 0402  Multilayer Ceramic Capacitors MLCC - SMD/SMT ROHS","0402 (1005 Metric)","Surface Mount "
"C4,C5,C6,C8,C9,C10,C13,C20,C21,C25,C26,C28","10uF","12","Murata Electronics","GRM155C80J106ME11D","6.3V 10uF X6S ±20% 0402  Multilayer Ceramic Capacitors MLCC - SMD/SMT ROHS","0402 (1005 Metric)","Surface Mount "
"C3,C7,C17,C27","1uF","4","Murata Electronics","GRM155C71A105ME11D","10V 1uF X7S 0402  Multilayer Ceramic Capacitors MLCC - SMD/SMT ROHS","0402 (1005 Metric)","Surface Mount "
"C1,C2","12pF","2","Samsung Electro-Mechanics","CL05C120JB5NNNC","50V 12pF C0G ±5% 0402  Multilayer Ceramic Capacitors MLCC - SMD/SMT ROHS","0402 (1005 Metric)","Surface Mount "
"J2","USB","1","CUI Devices","UJ20-C-G-MSMT-TR-68","USB-C (USB TYPE-C) USB 2.0 Receptacle Connector Mid-mount","SMD-8","Surface Mount"
